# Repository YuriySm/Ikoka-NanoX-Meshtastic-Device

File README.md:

Українська версія 🇺🇦 README доступна в [README_UK-UA.md](README_UK-UA.md).

Ikoka NanoX (eXtended) Meshtastic PCB is a fork of the [Ikoka Nano Meshtastic Device](https://github.com/ndoo/ikoka-nano-meshtastic-device) created by [Andrew Yong](https://ndoo.sg/projects:amateur_radio:meshtastic:diy_devices:ikoka_nano). This is a modified version of the original design released under CERN-OHL-P.

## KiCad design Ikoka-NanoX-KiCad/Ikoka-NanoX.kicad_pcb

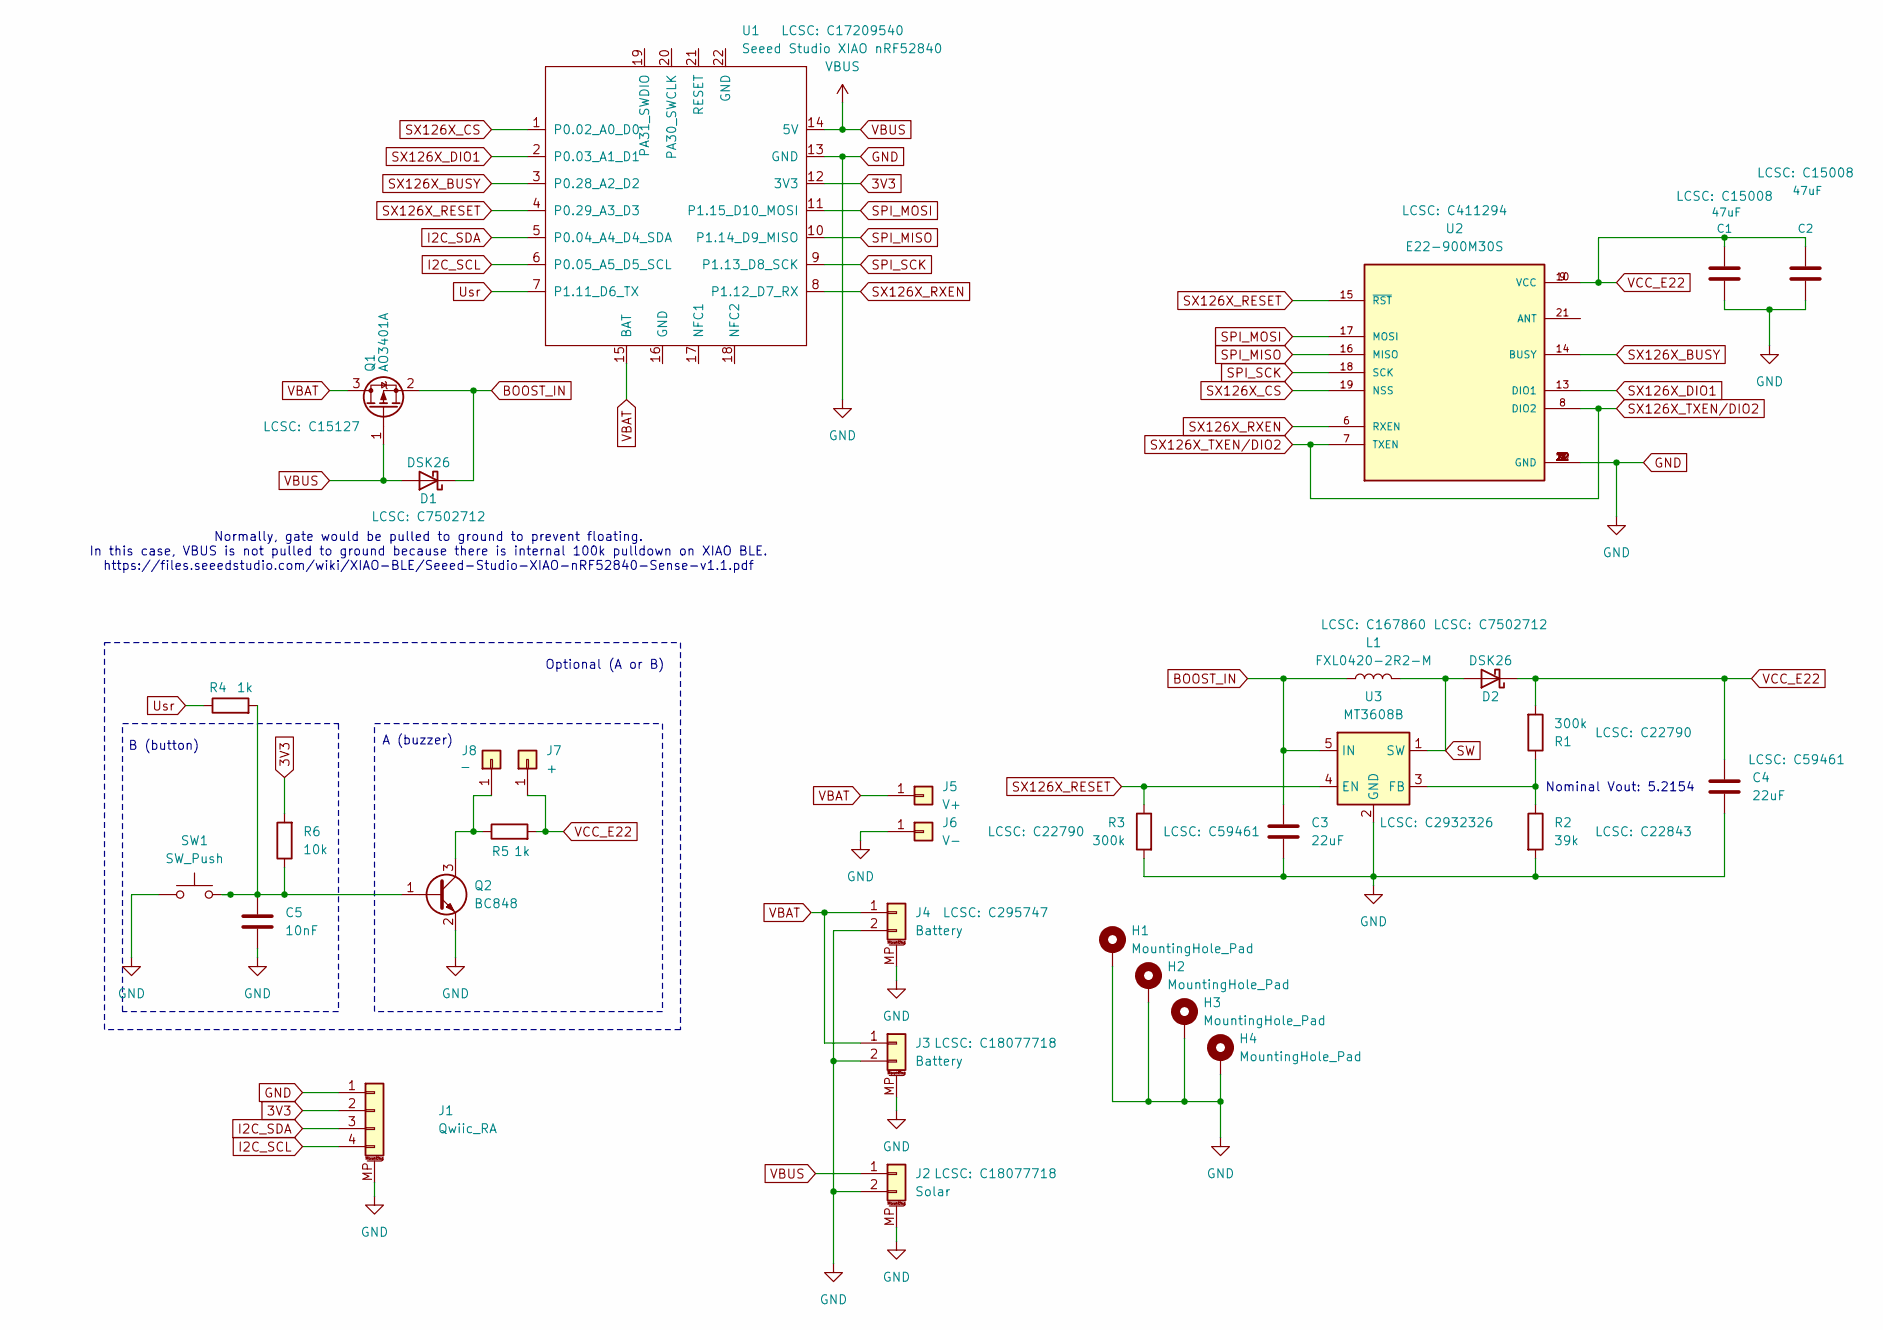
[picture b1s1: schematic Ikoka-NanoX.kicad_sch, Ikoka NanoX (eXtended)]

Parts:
C1, C2: 47uF; C_0805_2012Metric_Pad1.18x1.45mm_HandSolder; MPN CL31A107MQHNNNE; LCSC C15008
C3, C4: 22uF; C_0603_1608Metric_Pad1.08x0.95mm_HandSolder; MPN CL10A226MQ8NRNC; LCSC C59461
C5: 10nF; C_0603_1608Metric_Pad1.08x0.95mm_HandSolder; MPN CL10A226MQ8NRNC
D1, D2: DSK26; D_SOD-123F; LCSC C7502712
H1, H2, H3, H4: MountingHole_Pad; MountingHole_2.7mm_M2.5_Pad_Via
J1: Qwiic_RA; JST_SH_SM04B-SRSS-TB_1x04-1MP_P1.00mm_Horizontal
J2: Solar; Molex_PicoBlade_53261-0271_1x02-1MP_P1.25mm_Horizontal; LCSC C18077718
J3: Battery; Molex_PicoBlade_53261-0271_1x02-1MP_P1.25mm_Horizontal; LCSC C18077718
J4: Battery; Molex_PicoBlade_53398-0271_1x02-1MP_P1.25mm_Vertical; LCSC C295747
J5: V+; SolderWirePad_1x01_SMD_1x2mm
J6: V-; SolderWirePad_1x01_SMD_1x2mm
J7: +; SolderWirePad_1x01_SMD_1x2mm
J8: -; SolderWirePad_1x01_SMD_1x2mm
L1: FXL0420-2R2-M; L_Changjiang_FXL0420; MPN SMMS0650-220M; LCSC C167860
Q1: AO3401A; SOT-23; LCSC C15127
Q2: BC848; SOT-23
R1, R3: 300k; R_0603_1608Metric_Pad0.98x0.95mm_HandSolder; MPN 0603WAF1502T5E; LCSC C22790
R2: 39k; R_0603_1608Metric_Pad0.98x0.95mm_HandSolder; MPN 0603WAF1871T5E; LCSC C22843
R4, R5: 1k; R_0603_1608Metric_Pad0.98x0.95mm_HandSolder
R6: 10k; R_0603_1608Metric_Pad0.98x0.95mm_HandSolder
SW1: SW_Push; SW_SPST_FSMSM
U1: Seeed Studio XIAO nRF52840; XIAO-nRF52840-SMD_Handsoldering; LCSC C17209540
U2: E22-900M30S; XCVR_E22-900M30S; PARTREV 1.2; LCSC C411294
U3: MT3608B; SOT-23-6; LCSC C2932326

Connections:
3V3: J1.2, R6.2, U1.12 (3V3)
BOOST_IN: C3.1, D1.1 (K), L1.1, Q1.2 (S), U3.5 (IN)
GND: C1.1, C2.1, C3.2, C4.2, C5.2, H1.1, H2.1, H3.1, H4.1, J1.1, J1.MP (MountPin), J2.2, J2.MP (MountPin), J3.2, J3.MP (MountPin), J4.2, J4.MP (MountPin), J6.1, Q2.2 (E), R2.2, R3.2, SW1.1, U1.13 (GND), U2.1 (GND), U2.2 (GND), U2.3 (GND), U2.4 (GND), U2.5 (GND), U2.11 (GND), U2.12 (GND), U2.20 (GND), U2.22 (GND), U3.2 (GND)
I2C_SCL: J1.4, U1.6 (P0.05_A5_D5_SCL)
I2C_SDA: J1.3, U1.5 (P0.04_A4_D4_SDA)
unnamed: J8.1, Q2.3 (C), R5.1
unnamed: C5.1, Q2.1 (B), R4.2, R6.1, SW1.2
unnamed: R1.1, R2.1, U3.3 (FB)
SPI_MISO: U1.10 (P1.14_D9_MISO), U2.16 (MISO)
SPI_MOSI: U1.11 (P1.15_D10_MOSI), U2.17 (MOSI)
SPI_SCK: U1.9 (P1.13_D8_SCK), U2.18 (SCK)
SW: D2.2 (A), L1.2, U3.1 (SW)
SX126X_BUSY: U1.3 (P0.28_A2_D2), U2.14 (BUSY)
SX126X_CS: U1.1 (P0.02_A0_D0), U2.19 (NSS)
SX126X_DIO1: U1.2 (P0.03_A1_D1), U2.13 (DIO1)
SX126X_RESET: R3.1, U1.4 (P0.29_A3_D3), U2.15 (~RST), U3.4 (EN)
SX126X_RXEN: U1.8 (P1.12_D7_RX), U2.6 (RXEN)
SX126X_TXEN/DIO2: U2.7 (TXEN), U2.8 (DIO2)
Usr: R4.1, U1.7 (P1.11_D6_TX)
VBAT: J3.1, J4.1, J5.1, Q1.3 (D), U1.15 (BAT)
VBUS: D1.2 (A), J2.1, Q1.1 (G), U1.14 (5V)
VCC_E22: C1.2, C2.2, C4.1, D2.1 (K), J7.1, R1.2, R5.2, U2.9 (VCC), U2.10 (VCC)

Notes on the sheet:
A (buzzer)
Nominal Vout: 5.2154
B (button)
Normally, gate would be pulled to ground to prevent floating. In this case, VBUS is not pulled to ground because there is internal 100k pulldown on XIAO BLE. https://files.seeedstudio.com/wiki/XIAO-BLE/Seeed-Studio-XIAO-nRF52840-Sense-v1.1.pdf
Optional (A or B)

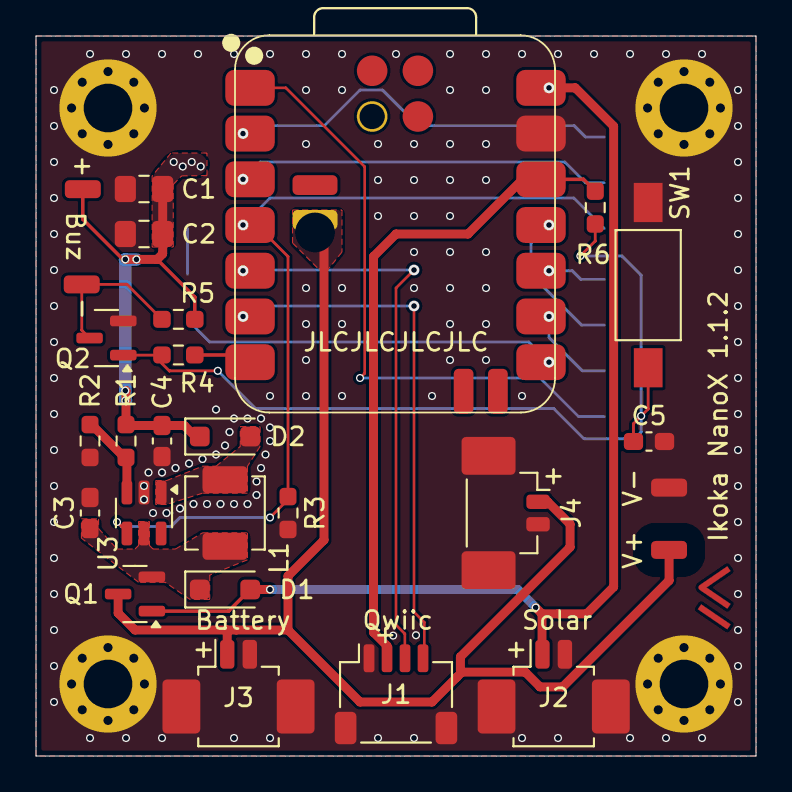
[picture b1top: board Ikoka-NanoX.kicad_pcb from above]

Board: 2 copper layers, 40.0 x 40.0 mm, 33 parts (1 on the bottom side), 22 nets.

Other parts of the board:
SYM1: Meshtastic Logo; meshtastic_logo

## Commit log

2025-10-11 Fork from original ikoka Nano by Andrew Yong. PCB and schematic additions.
2025-10-11 README updated
2025-10-18 README updated, KiCad improvements
2025-10-27 removed rounded corners, as less stable in the case
